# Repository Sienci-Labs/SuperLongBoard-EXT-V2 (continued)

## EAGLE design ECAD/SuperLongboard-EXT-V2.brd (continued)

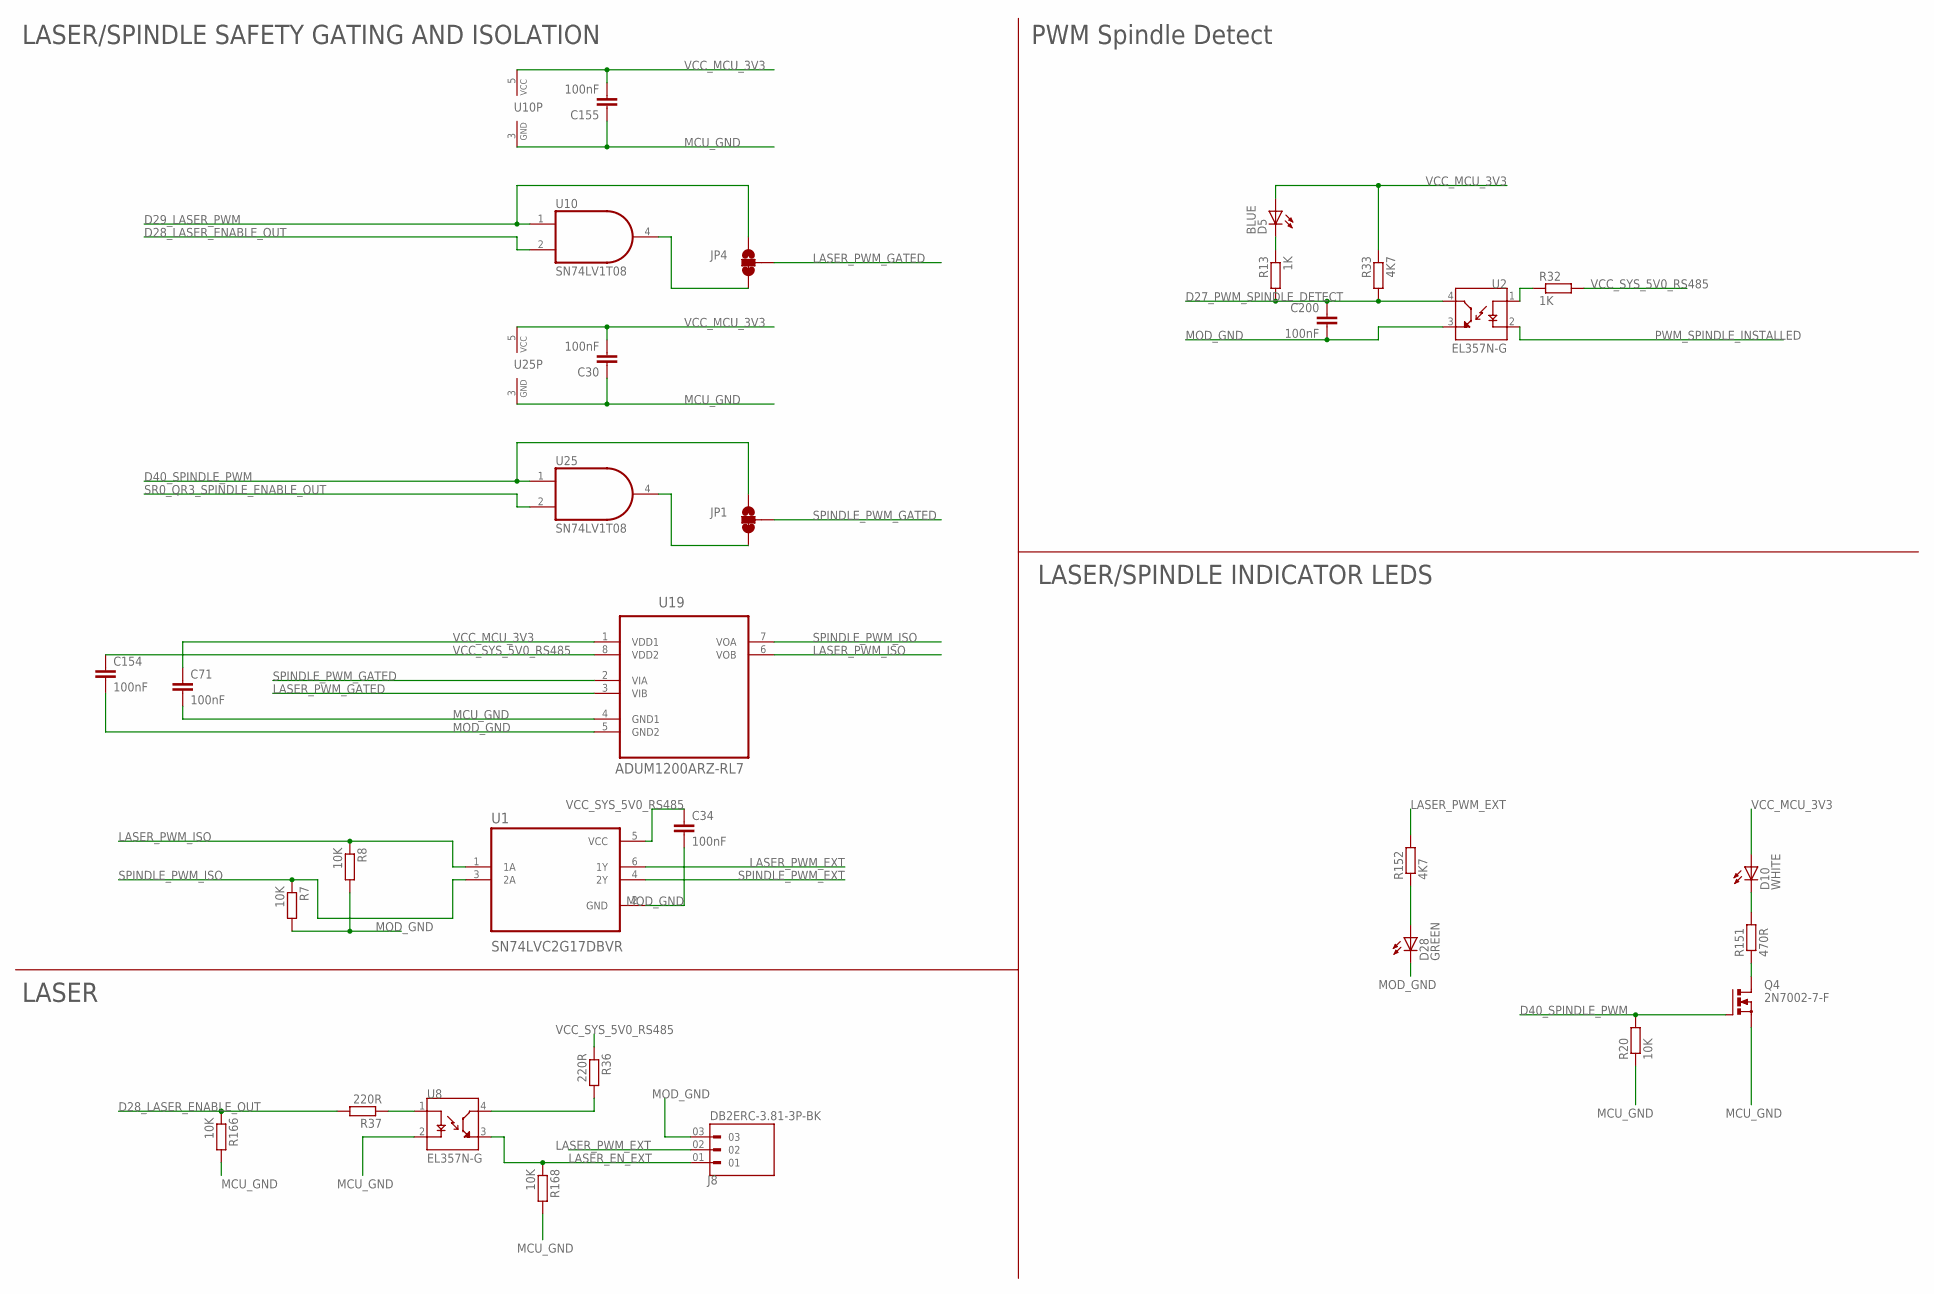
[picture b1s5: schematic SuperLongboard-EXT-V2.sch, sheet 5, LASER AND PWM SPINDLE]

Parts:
C30, C155, C200: 100nF; C0603
C34: 100nF; C0603; LCSC_PART C14663
C71, C154: 100nF; C0603K
D5: BLUE; CHIP-LED0805
D10: WHITE; CHIP-LED0805
D28: GREEN; CHIP-LED0805
J8: DB2ERC-3.81-3P-BK; PHOENIX_1803280
JP1, JP4: DNI; SMT-JUMPER_3_1-NC_TRACE_SILK
Q4: 2N7002-7-F; SOT-23
R7, R8, R20, R166, R168: 10K; R0603
R13, R32: 1K; R0603
R33, R152: 4K7; R0603
R36, R37: 220R; R0603
R151: 470R; R0603
U1: SN74LVC2G17DBVR; SOT95P280X145-6N
U2, U8: EL357N-G; OPTO_EL357N-G
U10, U25: SN74LV1T08; SOT23-5
U19: ADUM1200ARZ-RL7; SOIC127P600X175-8N

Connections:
D27_PWM_SPINDLE_DETECT: C200.1, R13.2, R33.2, U2.4 (CT); also elsewhere on the board
D28_LASER_ENABLE_OUT: R37.2, R166.1, U10.2 (I1); also elsewhere on the board
D29_LASER_PWM: JP4.1, U10.1 (I0); also elsewhere on the board
D40_SPINDLE_PWM: JP1.1, Q4.P1 (G), R20.2, U25.1 (I0); also elsewhere on the board
LASER_EN_EXT: J8.01, R168.1, U8.3 (ET)
LASER_PWM_EXT: J8.02, R152.2, U1.6 (1Y)
LASER_PWM_GATED: JP4.2, U19.3 (VIB)
LASER_PWM_ISO: R8.1, U1.1 (1A), U19.6 (VOB)
MCU_GND: C30.1, C71.2, C155.1, Q4.P2 (S), R20.1, R166.2, R168.2, U8.2 (C), U10.3 (GND), U19.4 (GND1), U25.3 (GND); also elsewhere on the board
MOD_GND: C34.2, C154.2, C200.2, D28.C, J8.03, R7.2, R8.2, U1.2 (GND), U2.3 (ET), U19.5 (GND2); also elsewhere on the board
unnamed: R32.1, U2.1 (A)
unnamed: JP1.3, U25.4 (O)
unnamed: D10.C, R151.2
unnamed: Q4.P3 (D), R151.1
unnamed: JP4.3, U10.4 (O)
unnamed: D5.C, R13.1
unnamed: D28.A, R152.1
unnamed: R37.1, U8.1 (A)
unnamed: R36.2, U8.4 (CT)
PWM_SPINDLE_INSTALLED: U2.2 (C); also elsewhere on the board
SPINDLE_PWM_EXT: U1.4 (2Y); also elsewhere on the board
SPINDLE_PWM_GATED: JP1.2, U19.2 (VIA)
SPINDLE_PWM_ISO: R7.1, U1.3 (2A), U19.7 (VOA)
SR0_QR3_SPINDLE_ENABLE_OUT: U25.2 (I1); also elsewhere on the board
VCC_MCU_3V3: C30.2, C71.1, C155.2, D5.A, D10.A, R33.1, U10.5 (VCC), U19.1 (VDD1), U25.5 (VCC); also elsewhere on the board
VCC_SYS_5V0_RS485: C34.1, C154.1, R32.2, R36.1, U1.5 (VCC), U19.8 (VDD2); also elsewhere on the board

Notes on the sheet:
LASER
PWM Spindle Detect
LASER/SPINDLE SAFETY GATING AND ISOLATION
LASER/SPINDLE INDICATOR LEDS

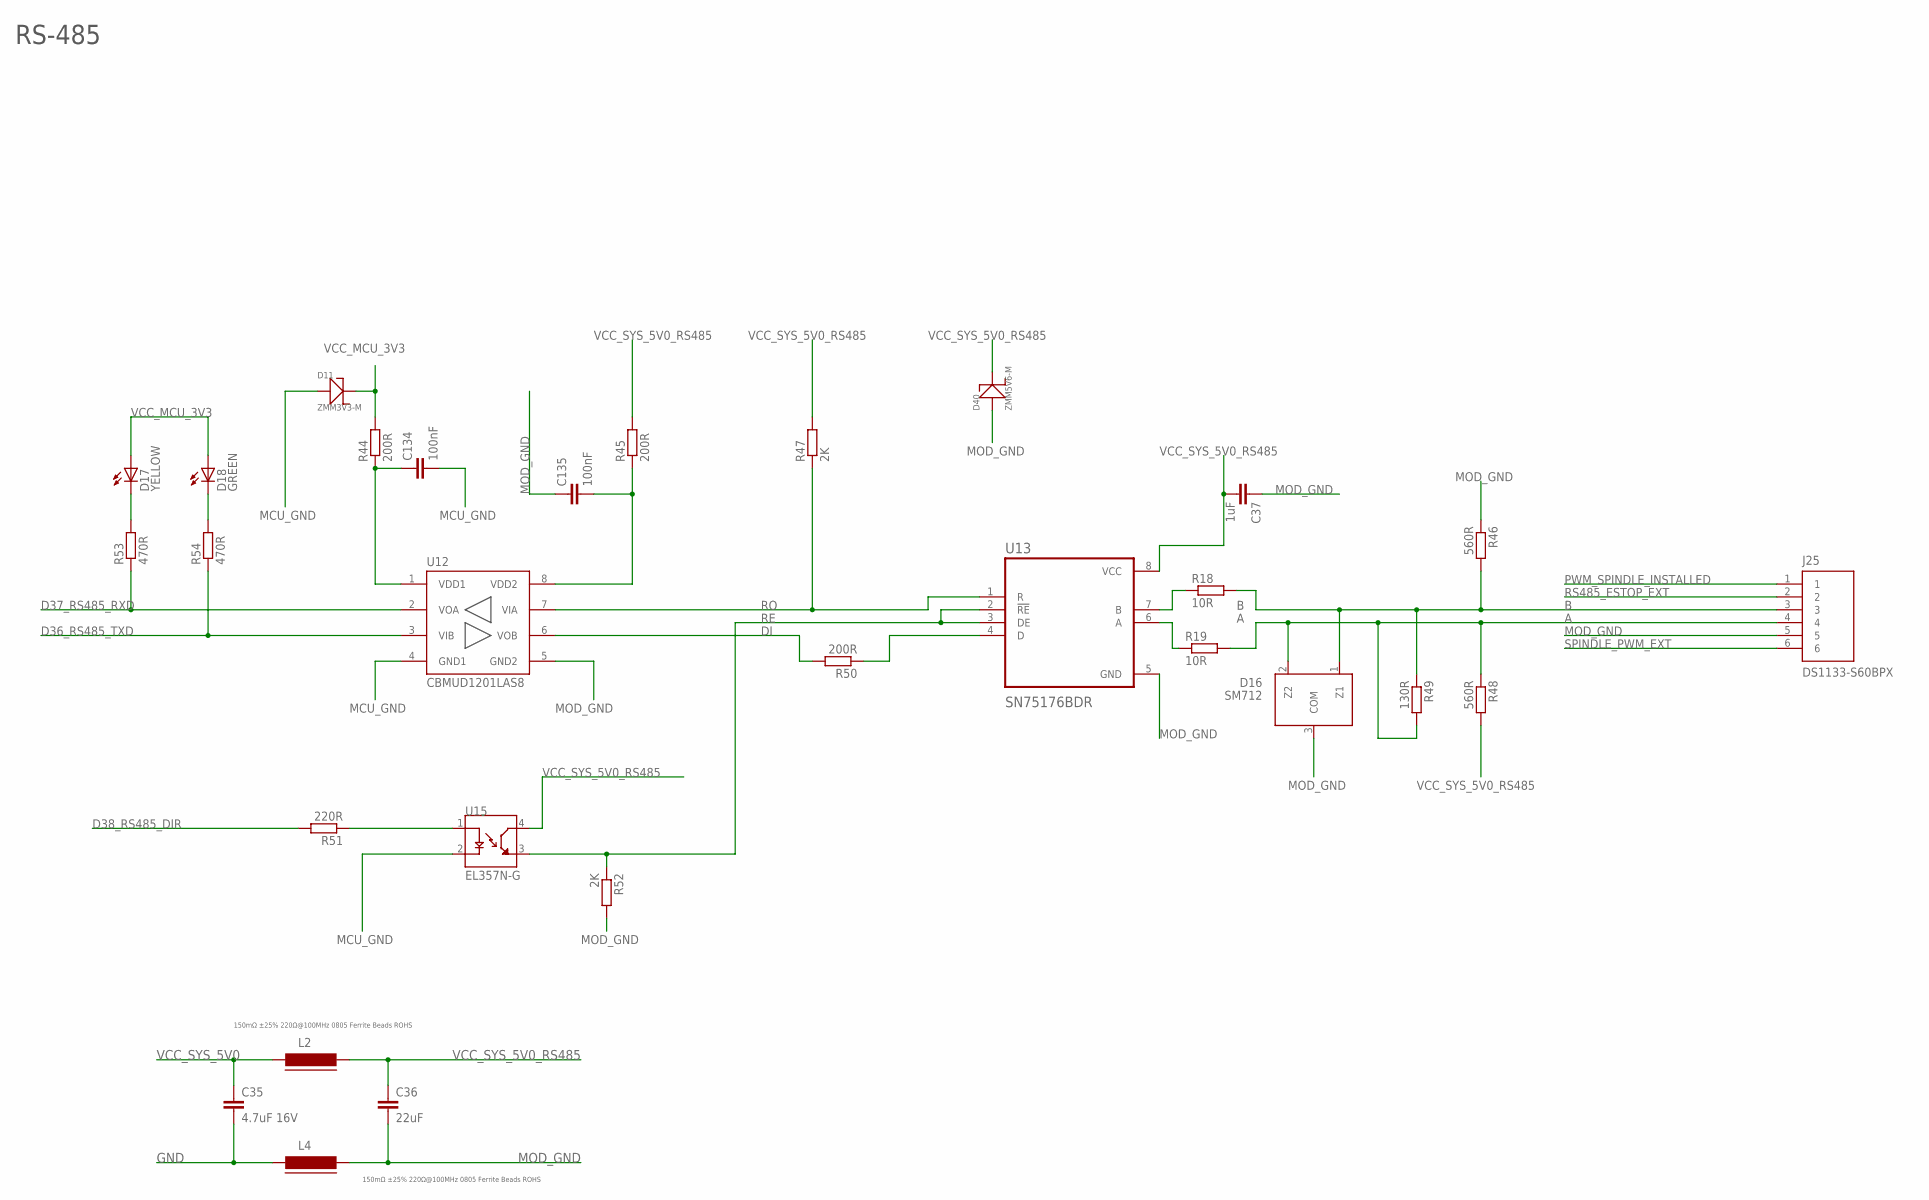
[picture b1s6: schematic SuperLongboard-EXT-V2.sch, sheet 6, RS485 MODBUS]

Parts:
C35: 4.7uF 16V; C0603
C36: 22uF; C0603; LCSC_PART C59461
C37: 1uF; C0603; LCSC_PART C15849
C134, C135: 100nF; C0603; LCSC_PART C14663
D11: ZMM3V3-M; LL-34
D16: SM712; SOT23
D17: YELLOW; CHIP-LED0805
D18: GREEN; CHIP-LED0805
D40: ZMM5V6-M; LL-34
J25: DS1133-S60BPX; KH-PCB-6P6C
L2, L4: 150mΩ ±25% 220Ω@100MHz 0805 Ferrite Beads ROHS; FB805; LCSC_PART C139188
R18, R19: 10R; R0603
R44, R45, R50: 200R; R0603
R46, R48: 560R; R0603
R47, R52: 2K; R0603
R49: 130R; R0805
R51: 220R; R0603
R53, R54: 470R; R0603
U12: CBMUD1201LAS8; SOIC-8
U13: SN75176BDR; SOIC127P599X175-8N
U15: EL357N-G; OPTO_EL357N-G

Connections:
A: D16.2 (Z2), J25.4, R19.2, R48.1, R49.2
B: D16.1 (Z1), J25.3, R18.2, R46.2, R49.1
D36_RS485_TXD: R54.1, U12.3 (VIB); also elsewhere on the board
D37_RS485_RXD: R53.1, U12.2 (VOA); also elsewhere on the board
D38_RS485_DIR: R51.2; also elsewhere on the board
DI: R50.2, U12.6 (VOB)
GND: C35.2, L4.1; also elsewhere on the board
MCU_GND: C134.2, D11.A (+), U12.4 (GND1), U15.2 (C); also elsewhere on the board
MOD_GND: C36.2, C37.1, C135.1, D16.3 (COM), D40.A (+), J25.5, L4.2, R46.1, R52.2, U12.5 (GND2), U13.5 (GND); also elsewhere on the board
unnamed: R18.1, U13.7 (B)
unnamed: R19.1, U13.6 (A)
unnamed: C134.1, R44.1, U12.1 (VDD1)
unnamed: C135.2, R45.1, U12.8 (VDD2)
unnamed: R50.1, U13.4 (D)
unnamed: R51.1, U15.1 (A)
unnamed: D17.C, R53.2
unnamed: D18.C, R54.2
PWM_SPINDLE_INSTALLED: J25.1; also elsewhere on the board
RE: R52.1, U13.2 (!RE), U13.3 (DE), U15.3 (ET)
RO: R47.1, U12.7 (VIA), U13.1 (R)
RS485_ESTOP_EXT: J25.2; also elsewhere on the board
SPINDLE_PWM_EXT: J25.6; also elsewhere on the board
VCC_MCU_3V3: D11.C (-), D17.A, D18.A, R44.2; also elsewhere on the board
VCC_SYS_5V0: C35.1, L2.1; also elsewhere on the board
VCC_SYS_5V0_RS485: C36.1, C37.2, D40.C (-), L2.2, R45.2, R47.2, R48.2, U13.8 (VCC), U15.4 (CT); also elsewhere on the board

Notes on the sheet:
RS-485

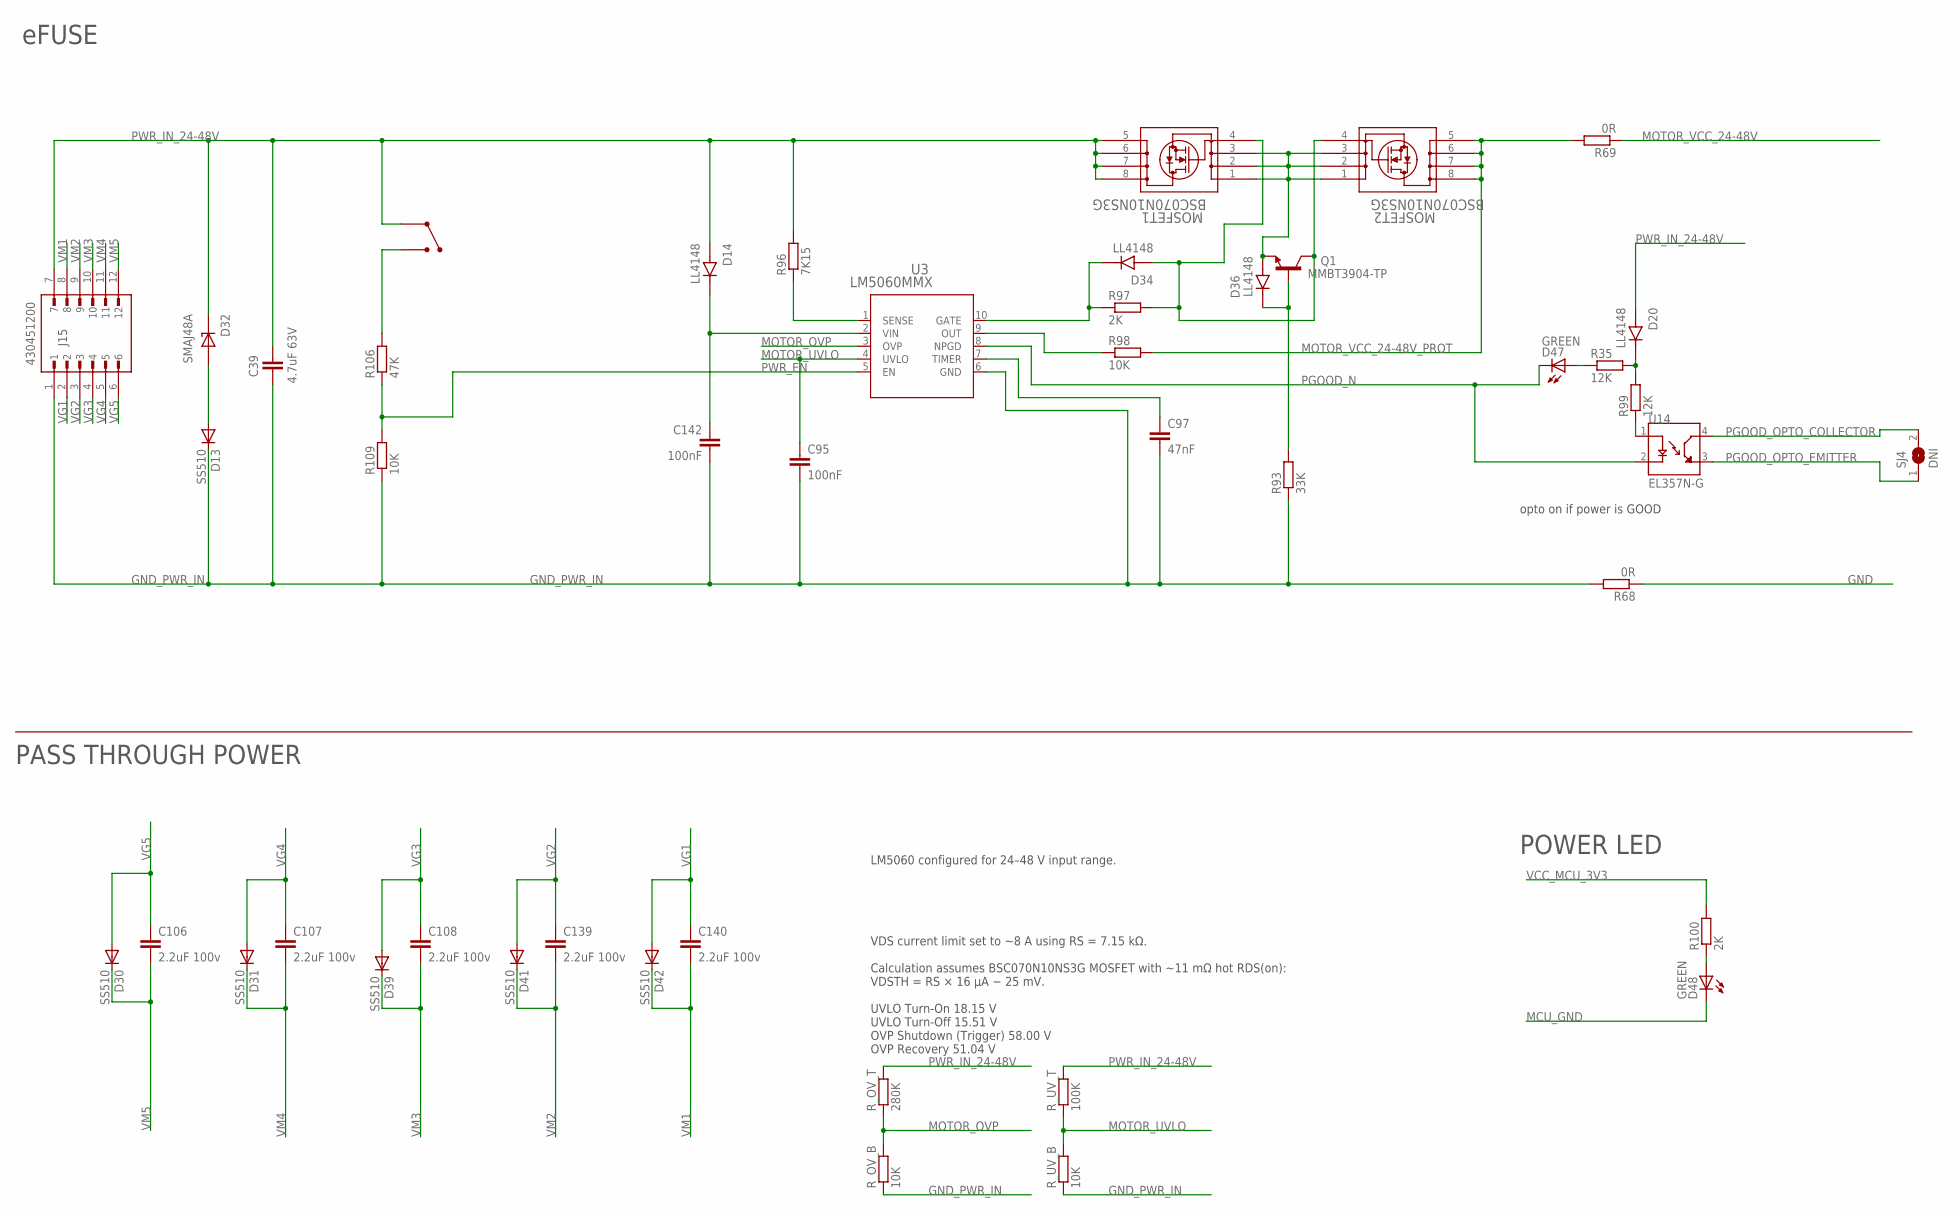
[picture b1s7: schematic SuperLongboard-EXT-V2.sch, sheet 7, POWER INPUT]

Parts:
C39: 4.7uF 63V; C1210; LCSC_PART C47783
C95, C142: 100nF; C0603; LCSC_PART C28233
C97: 47nF; C0805; LCSC_PART C53134
C106, C107, C108, C139, C140: 2.2uF 100v; C1210; LCSC_PART C576517
D13, D30, D31, D39, D41, D42: SS510; DO-214AC
D14, D20, D34, D36: LL4148; DIO_LL4148
D32: SMAJ48A; DIOM4325X250N
D47, D48: GREEN; CHIP-LED0805
J15: 430451200; MOLEX_430451200
MOSFET1, MOSFET2: BSC070N10NS3G; QNMOS_PRPAK5X6_HUA
Q1: MMBT3904-TP; SOT95P237X125-3N
R35, R99: 12K; R0805
R68, R69: 0R; R0603
R93: 33K; R0805
R96: 7K15; R1206
R97, R100: 2K; R0603
R98, R109: 10K; R0603
R106: 47K; R0805
R_OV_B: 10K; R0603
R_OV_T: 280K; R0805
R_UV_B: 10K; R0603
R_UV_T: 100K; R0805
SJ4: DNI; SJ
SW1: KCD11-BL
U3: LM5060MMX; MUB10A
U14: EL357N-G; OPTO_EL357N-G

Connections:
GND: R68.1; also elsewhere on the board
GND_PWR_IN: C39.2, C95.2, C97.2, C142.2, D13.C, J15.1, R68.2, R93.1, R109.1, R_OV_B.1, R_UV_B.1, U3.6 (GND)
MCU_GND: D48.C; also elsewhere on the board
MOTOR_OVP: R_OV_B.2, R_OV_T.1, U3.3 (OVP)
MOTOR_UVLO: C95.1, R_UV_B.2, R_UV_T.1, U3.4 (UVLO)
MOTOR_VCC_24-48V: R69.1; also elsewhere on the board
MOTOR_VCC_24-48V_PROT: MOSFET2.5, MOSFET2.6, MOSFET2.7, MOSFET2.8, R69.2, R98.2
unnamed: D47.A, R35.1
unnamed: R96.1, U3.1 (SENSE)
unnamed: D34.C, R97.1, U3.10 (GATE)
unnamed: D36.C, Q1.1 (B), R93.2
unnamed: R98.1, U3.9 (OUT)
unnamed: C97.1, U3.7 (TIMER)
unnamed: D20.C, R35.2, R99.2
unnamed: D34.A, MOSFET1.4, MOSFET2.4, Q1.3 (C), R97.2
unnamed: C142.1, D14.C, U3.2 (VIN)
unnamed: D13.A, D32.A
unnamed: R99.1, U14.1 (A)
unnamed: D36.A, MOSFET1.1, MOSFET1.2, MOSFET1.3, MOSFET2.1, MOSFET2.2, MOSFET2.3, Q1.2 (E)
unnamed: D48.A, R100.1
unnamed: R106.2, SW1.P$2
PGOOD_N: D47.C, U3.8 (NPGD), U14.2 (C)
PGOOD_OPTO_COLLECTOR: SJ4.2, U14.4 (CT); also elsewhere on the board
PGOOD_OPTO_EMITTER: SJ4.1, U14.3 (ET); also elsewhere on the board
PWR_EN: R106.1, R109.2, U3.5 (EN)
PWR_IN_24-48V: C39.1, D14.A, D20.A, D32.C, J15.7, MOSFET1.5, MOSFET1.6, MOSFET1.7, MOSFET1.8, R96.2, R_OV_T.2, R_UV_T.2, SW1.P$1
VCC_MCU_3V3: R100.2; also elsewhere on the board
VG1: C140.1, D42.A, J15.2; also elsewhere on the board
VG2: C139.1, D41.A, J15.3; also elsewhere on the board
VG3: C108.1, D39.A, J15.4; also elsewhere on the board
VG4: C107.1, D31.A, J15.5; also elsewhere on the board
VG5: C106.1, D30.A, J15.6; also elsewhere on the board
VM1: C140.2, D42.C, J15.8; also elsewhere on the board
VM2: C139.2, D41.C, J15.9; also elsewhere on the board
VM3: C108.2, D39.C, J15.10; also elsewhere on the board
VM4: C107.2, D31.C, J15.11; also elsewhere on the board
VM5: C106.2, D30.C, J15.12; also elsewhere on the board

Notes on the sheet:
eFUSE
LM5060 configured for 24–48 V input range. VDS current limit set to ~8 A using RS = 7.15 kΩ. Calculation assumes BSC070N10NS3G MOSFET with ~11 mΩ hot RDS(on): VDSTH = RS × 16 µA − 25 mV. UVLO Turn-On 18.15 V UVLO Turn-Off 15.51 V OVP Shutdown (Trigger) 58.00 V OVP Recovery 51.04 V
opto on if power is GOOD
POWER LED
PASS THROUGH POWER

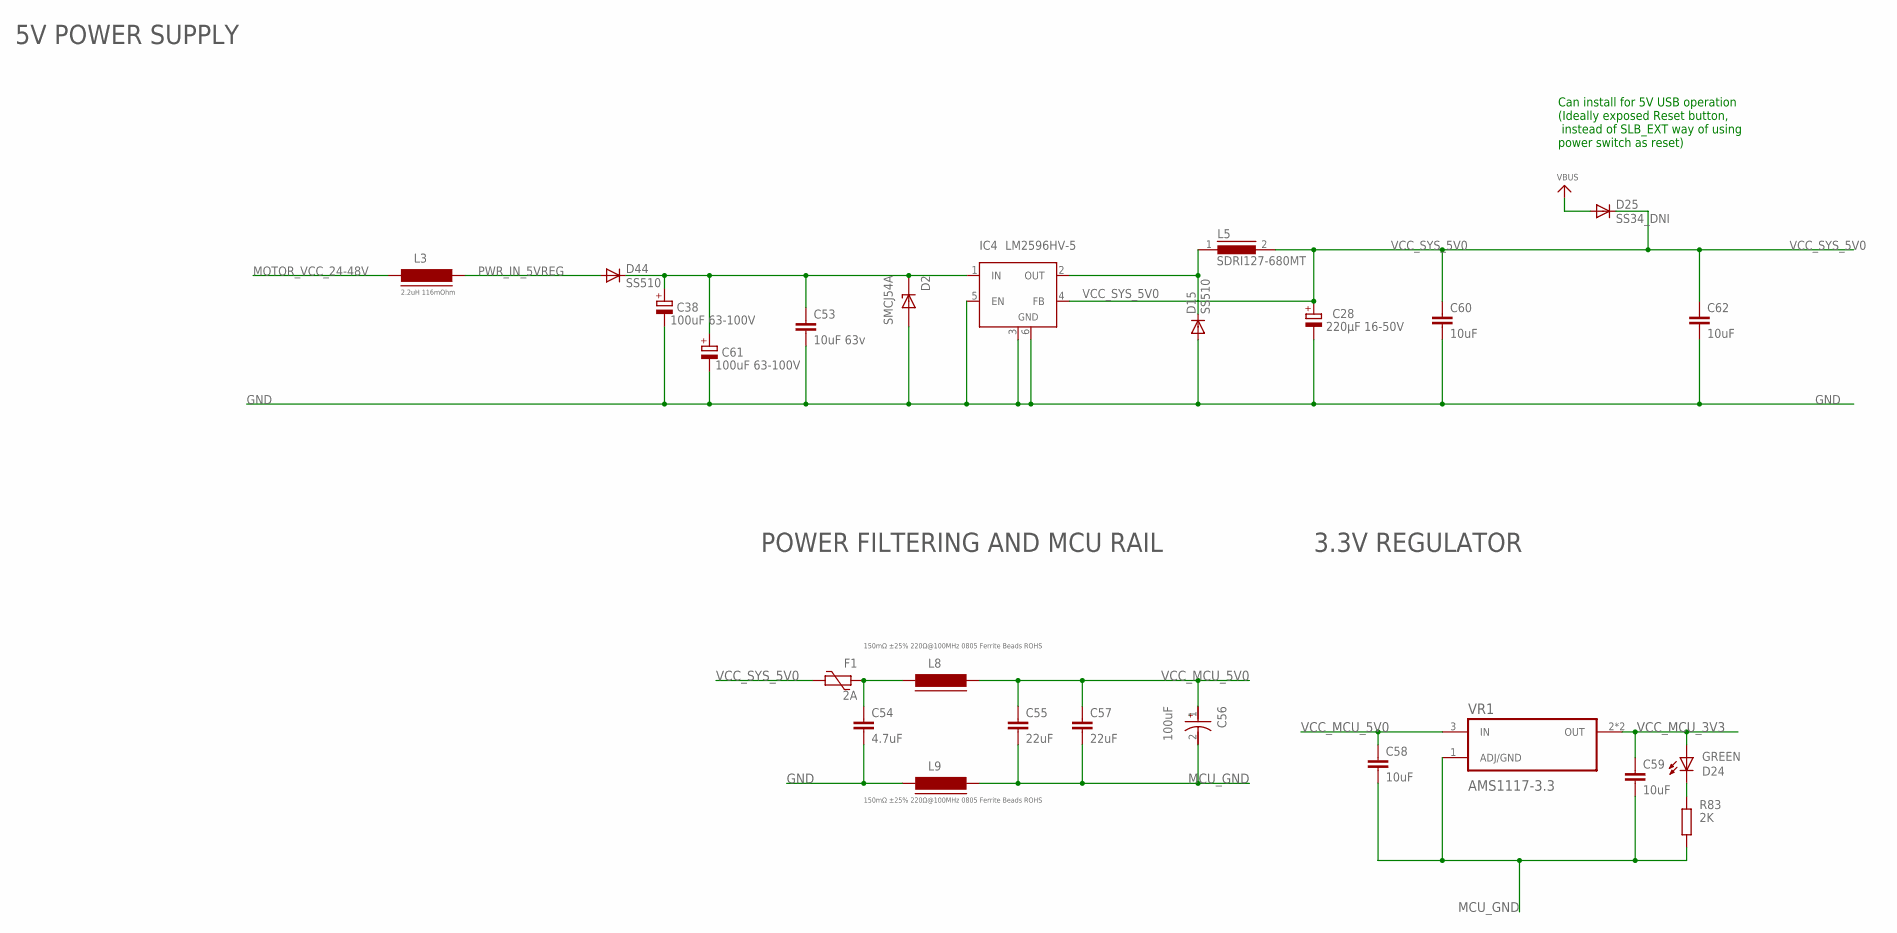
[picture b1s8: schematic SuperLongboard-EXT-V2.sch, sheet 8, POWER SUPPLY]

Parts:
C28: 220µF 16-50V; PANASONIC_E
C38, C61: 100uF 63-100V; PANASONIC_E
C53: 10uF 63v; C1206; LCSC_PART C13585
C54: 4.7uF; C0603
C55, C57: 22uF; C0603; LCSC_PART C59461
C56: 100uF; CAPMP3528X210N
C58, C59, C60, C62: 10uF; C1206; LCSC_PART C13585
D2: SMCJ54A; DIOM7959X262N
D15, D44: SS510; DO-214AC
D24: GREEN; CHIP-LED0805
D25: SS34_DNI; DO-214AC
F1: 2A; 1206L
IC4: LM2596HV-5; TO263-5
L3: 2.2uH 116mOhm; FB805; LCSC_PART C139188
L5: SDRI127-680MT; DR127
L8, L9: 150mΩ ±25% 220Ω@100MHz 0805 Ferrite Beads ROHS; FB805; LCSC_PART C139188
R83: 2K; R0603
VR1: AMS1117-3.3

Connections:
+24V1: C38.+, C53.1, C61.+, D2.C, D44.C, IC4.1 (IN)
GND: C28.-, C38.-, C53.2, C54.2, C60.2, C61.-, C62.2, D2.A, D15.A, IC4.3 (GND), IC4.5 (EN), IC4.6 (GND), L9.1; also elsewhere on the board
MCU_GND: C55.2, C56.2, C57.2, C58.2, C59.2, L9.2, R83.2, VR1.1 (ADJ/GND); also elsewhere on the board
MOTOR_VCC_24-48V: L3.1; also elsewhere on the board
unnamed: D24.C, R83.1
unnamed: D15.C, IC4.2 (OUT), L5.1
PWR_IN_5VREG: D44.A, L3.2
SYS5V: C54.1, F1.2, L8.1
VBUS: D25.A; also elsewhere on the board
VCC_MCU_3V3: C59.1, D24.A, VR1.2 (OUT), VR1.4 (OUT); also elsewhere on the board
VCC_MCU_5V0: C55.1, C56.1, C57.1, C58.1, L8.2, VR1.3 (IN)
VCC_SYS_5V0: C28.+, C60.1, C62.1, D25.C, F1.1, IC4.4 (FB), L5.2; also elsewhere on the board

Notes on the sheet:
POWER FILTERING AND MCU RAIL
3.3V REGULATOR
5V POWER SUPPLY
Can install for 5V USB operation (Ideally exposed Reset button, instead of SLB_EXT way of using power switch as reset)

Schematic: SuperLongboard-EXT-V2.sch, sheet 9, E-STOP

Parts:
C3, C9, C13, C19, C20, C29, C31: 100nF; C0603; LCSC_PART C14663
D2_ESTOP_MCU: RED; CHIP-LED0805
E_STOPIN: 74HC08D-T; SOIC127P600X175-14N
J10: B2B-XH-A_(LF)(SN); JST_B2B-XH-A_(LF)(SN)
J11: DB2ERC-3.81-2P-BK; MC1.5/2-G-3.81
JP2: DNI; SMT-JUMPER_3_1-NC_TRACE_SILK
L12: 150mΩ ±25% 220Ω@100MHz 0805 Ferrite Beads ROHS; FB805; LCSC_PART C139188
R2, R34, R43, R56, R58, R64: 10K; R0603
R30, R40, R57: 510R; R0603
R38, R41: 120R; R0603
R55: 220R; R0603
R61: 2K; R0603
U11, U16, U22, U23: EL357N-G; OPTO_EL357N-G
U20_EGATE: 74HC08D-T; SOIC127P600X175-14N

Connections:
D28_LASER_ENABLE: U20_EGATE.2 (1B); also elsewhere on the board
D28_LASER_ENABLE_OUT: U20_EGATE.3 (1Y); also elsewhere on the board
D39_E_STOP/HALT: C19.1, E_STOPIN.11 (4Y), R61.1, R64.1, U20_EGATE.1 (1A), U20_EGATE.4 (2A), U20_EGATE.9 (3A), U20_EGATE.12 (4A), U22.2 (C); also elsewhere on the board
ESTOP1_LV: C13.1, E_STOPIN.1 (1A), R56.2, U16.3 (ET)
ESTOP3_LV: C3.1, E_STOPIN.4 (2A), R34.1, U11.4 (CT)
ESTOP5_LV: C31.1, E_STOPIN.9 (3A), R58.1, U23.4 (CT)
ESTOP_AUX: U11.2 (C); also elsewhere on the board
ESTOP_CONTROLLER: J10.1, R40.2
ESTOP_EXT: J11.1, R57.2
GND: U16.2 (C), U23.2 (C); also elsewhere on the board
MCU_GND: C3.2, C9.2, C13.2, C19.2, C20.2, C29.2, C31.2, E_STOPIN.7 (GND), R2.1, R56.1, U11.3 (ET), U20_EGATE.7 (GND), U23.3 (ET); also elsewhere on the board
MOD_GND: U22.3 (ET); also elsewhere on the board
unnamed: R30.1, U11.1 (A)
unnamed: R55.1, U22.1 (A)
unnamed: R40.1, U16.1 (A)
unnamed: E_STOPIN.6 (2Y), E_STOPIN.10 (3B)
unnamed: E_STOPIN.3 (1Y), E_STOPIN.12 (4A)
unnamed: E_STOPIN.8 (3Y), E_STOPIN.13 (4B)
unnamed: R41.1, U16.4 (CT)
unnamed: R57.1, U23.1 (A)
unnamed: D2_ESTOP_MCU.C, R61.2
unnamed: JP2.1, U20_EGATE.11 (4Y)
PGOOD_OPTO_COLLECTOR: R38.1; also elsewhere on the board
PGOOD_OPTO_EMITTER: C9.1, E_STOPIN.2 (1B), R2.2; also elsewhere on the board
RS485_ESTOP_EXT: U22.4 (CT); also elsewhere on the board
SPARE_ESTOP: E_STOPIN.5 (2B), R43.1
SR0_Q0_XYA_ENABLE: U20_EGATE.10 (3B); also elsewhere on the board
SR0_Q0_XYA_ENABLE_OUT: U20_EGATE.8 (3Y); also elsewhere on the board
SR0_Q1_Z_ENABLE: JP2.3, U20_EGATE.13 (4B); also elsewhere on the board
SR0_Q1_Z_ENABLE_OUT: JP2.2; also elsewhere on the board
SR0_QR3_SPINDLE_ENABLE: U20_EGATE.5 (2B); also elsewhere on the board
SR0_QR3_SPINDLE_ENABLE_OUT: U20_EGATE.6 (2Y); also elsewhere on the board
VCC_ESTOP_5V0: J10.2, J11.2, L12.1, R30.2
VCC_MCU_3V3: C20.1, C29.1, D2_ESTOP_MCU.A, E_STOPIN.14 (VCC), R34.2, R38.2, R41.2, R43.2, R55.2, R58.2, R64.2, U20_EGATE.14 (VCC); also elsewhere on the board
VCC_SYS_5V0: L12.2; also elsewhere on the board

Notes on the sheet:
HIGH - IF NO ESTOPS ARE ACTIVATED LOW - IF ANY ESTOP IS ACTIVATED
EMERGENCY STOPS
SIGNAL TO GRBLHAL
GATED ENABLE SIGNALS FOR CLS MOTORS, LASER, PWM SPINDLE
E-STOP OUTPUT FOR RS485 SPINDLE
PRIMARY E-STOP INPUT - CLOSED LOOP - OPENS ON PROBLEM
SIGNALS FROM MCU TO BE GATED BY E-STOP
PGOOD E-STOP INPUT -CLOSED LOOP - OPENS ON PROBLEM
AUX/ATCPTC E-STOP INPUT - OPEN LOOP - CLOSES ON PROBLEM
EXTERNAL/PANEL MOUNT/REMOTE E-STOP INPUT OPEN LOOP - CLOSES ON PROBLEM

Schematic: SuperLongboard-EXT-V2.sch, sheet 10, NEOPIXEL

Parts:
C101, C102: 100nF; C0603; LCSC_PART C14663
F4: 2A; 1206L
J6, J16: B3B-XH-A(LF)(SN); JST_B3B-XH-A(LF)(SN)
WC4, WC5, WC6, WC7, WC8, WC9, WC10, WC11, WC12, WC13, WC14, WC15: 100nF; C0603; LCSC_PART C14663
WL4, WL5, WL6, WL7, WL8, WL9, WL10, WL11, WL12, WL13, WL14, WL15: WS2812-2020; LED_WS2812-2020

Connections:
D35_NEOPIXEL_OUT: WL4.3 (DIN); also elsewhere on the board
GND: C101.2, C102.2, J6.1, J16.1, WC4.2, WC5.2, WC6.2, WC7.2, WC8.2, WC9.2, WC10.2, WC11.2, WC12.2, WC13.2, WC14.2, WC15.2, WL4.2 (VSS), WL5.2 (VSS), WL6.2 (VSS), WL7.2 (VSS), WL8.2 (VSS), WL9.2 (VSS), WL10.2 (VSS), WL11.2 (VSS), WL12.2 (VSS), WL13.2 (VSS), WL14.2 (VSS), WL15.2 (VSS); also elsewhere on the board
unnamed: WL4.1 (DOUT), WL5.3 (DIN)
unnamed: WL5.1 (DOUT), WL6.3 (DIN)
unnamed: WL6.1 (DOUT), WL7.3 (DIN)
unnamed: WL7.1 (DOUT), WL8.3 (DIN)
unnamed: WL8.1 (DOUT), WL9.3 (DIN)
unnamed: WL9.1 (DOUT), WL10.3 (DIN)
unnamed: WL10.1 (DOUT), WL11.3 (DIN)
unnamed: WL11.1 (DOUT), WL12.3 (DIN)
unnamed: WL12.1 (DOUT), WL13.3 (DIN)
unnamed: WL13.1 (DOUT), WL14.3 (DIN)
unnamed: WL14.1 (DOUT), WL15.3 (DIN)
unnamed: J6.2, J16.2, WL15.1 (DOUT)
NEOPIXEL_5V: C101.1, C102.1, F4.2, J6.3, J16.3, WC4.1, WC5.1, WC6.1, WC7.1, WC8.1, WC9.1, WC10.1, WC11.1, WC12.1, WC13.1, WC14.1, WC15.1, WL4.4 (VDD), WL5.4 (VDD), WL6.4 (VDD), WL7.4 (VDD), WL8.4 (VDD), WL9.4 (VDD), WL10.4 (VDD), WL11.4 (VDD), WL12.4 (VDD), WL13.4 (VDD), WL14.4 (VDD), WL15.4 (VDD)
VCC_SYS_5V0: F4.1; also elsewhere on the board

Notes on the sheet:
NEOPIXELS

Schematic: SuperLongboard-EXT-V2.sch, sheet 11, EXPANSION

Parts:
C93: 100nF; C0603; LCSC_PART C14663
IC1_SREXP: 74HC595; SOIC-16
J5: Connector IDC Header Through Hole 26 position 2.5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; 61202621621
R6, R59, R82: 100R; R0603
R65: 10k; R0603
R70: 100K; R0805

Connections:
D0_UART0_RX: J5.5; also elsewhere on the board
D1_UART0_TX: J5.7; also elsewhere on the board
D26_SR0_OE: IC1_SREXP.13 (!OE), J5.21, R65.1; also elsewhere on the board
D30_SDA: J5.11; also elsewhere on the board
D31_SCL: J5.13; also elsewhere on the board
D32_SR0_OUT: R6.1; also elsewhere on the board
D33_SR0_SCK: J5.15, R82.1; also elsewhere on the board
D34_SR0_LCK: J5.17, R59.1; also elsewhere on the board
D35_NEOPIXEL: J5.9; also elsewhere on the board
D41_ETHERNET_CS: J5.8, R70.1; also elsewhere on the board
D42_ETHERNET_IRQ: J5.10; also elsewhere on the board
D43_SPI_MOSI: J5.4; also elsewhere on the board
D44_SPI_MISO: J5.2; also elsewhere on the board
D46_SPI_SCK: J5.6; also elsewhere on the board
D47_SPARE: J5.14; also elsewhere on the board
ESTOP_AUX: J5.23; also elsewhere on the board
GND: C93.2, J5.1, J5.12, J5.26, R70.2; also elsewhere on the board
MCU_GND: IC1_SREXP.8 (GND); also elsewhere on the board
MOTOR_VCC_24-48V: J5.25; also elsewhere on the board
unnamed: IC1_SREXP.12 (LATCH), R59.2
unnamed: IC1_SREXP.11 (SCLK), R82.2
unnamed: IC1_SREXP.14 (SDA), R6.2
SR0_OUT: IC1_SREXP.9 (Q7S), J5.19
SR0_Q0_XYA_ENABLE: IC1_SREXP.15 (Q0); also elsewhere on the board
SR0_Q1_Z_ENABLE: IC1_SREXP.1 (Q1); also elsewhere on the board
SR0_Q2_COOLANT: IC1_SREXP.2 (Q2); also elsewhere on the board
SR0_QR3_SPINDLE_ENABLE: IC1_SREXP.3 (Q3), J5.16; also elsewhere on the board
SR0_QR4_SPARE: IC1_SREXP.4 (Q4), J5.18
SR0_QR5_SPARE: IC1_SREXP.5 (Q5), J5.20
SR0_QR6_SPARE: IC1_SREXP.6 (Q6), J5.22
SR0_QR7_SPARE: IC1_SREXP.7 (Q7), J5.24
VCC_MCU_3V3: C93.1, IC1_SREXP.10 (!RST), IC1_SREXP.16 (V+), R65.2; also elsewhere on the board
VCC_SYS_5V0: J5.3; also elsewhere on the board

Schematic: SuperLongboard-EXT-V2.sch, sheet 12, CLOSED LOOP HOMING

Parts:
C32, C52: 100nF; C0603K
D19, D29: GREEN; CHIP-LED0805
R39, R42: 200R; R0603
R60, R74: 2K; R0603
R62, R75: 10K; R0603
U4: ADUM1200ARZ-RL7; SOIC127P600X175-8N

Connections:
D24_XYA_HOME_EN: D19.C, R75.1, U4.2 (VIA); also elsewhere on the board
D25_Z_HOME_EN: D29.C, R62.1, U4.3 (VIB); also elsewhere on the board
GND: C52.2, U4.5 (GND2); also elsewhere on the board
MCU_GND: C32.2, U4.4 (GND1); also elsewhere on the board
unnamed: R39.2, U4.7 (VOA)
unnamed: R42.2, U4.6 (VOB)
unnamed: D29.A, R60.1
unnamed: D19.A, R74.1
VCC_MCU_3V3: C32.1, R60.2, R62.2, R74.2, R75.2, U4.1 (VDD1); also elsewhere on the board
VCC_SYS_5V0: C52.1, U4.8 (VDD2); also elsewhere on the board
XYA_HOME_EN: R39.1; also elsewhere on the board
Z_HOME_EN: R42.1; also elsewhere on the board

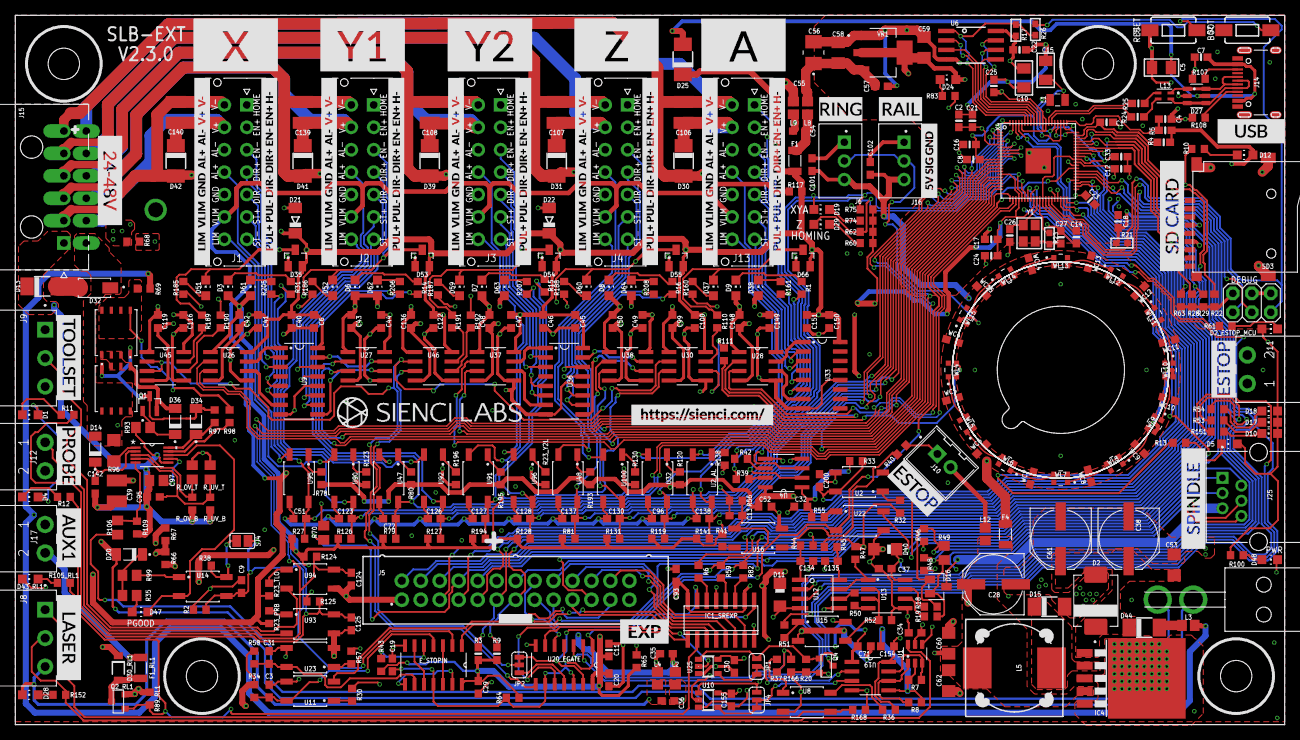
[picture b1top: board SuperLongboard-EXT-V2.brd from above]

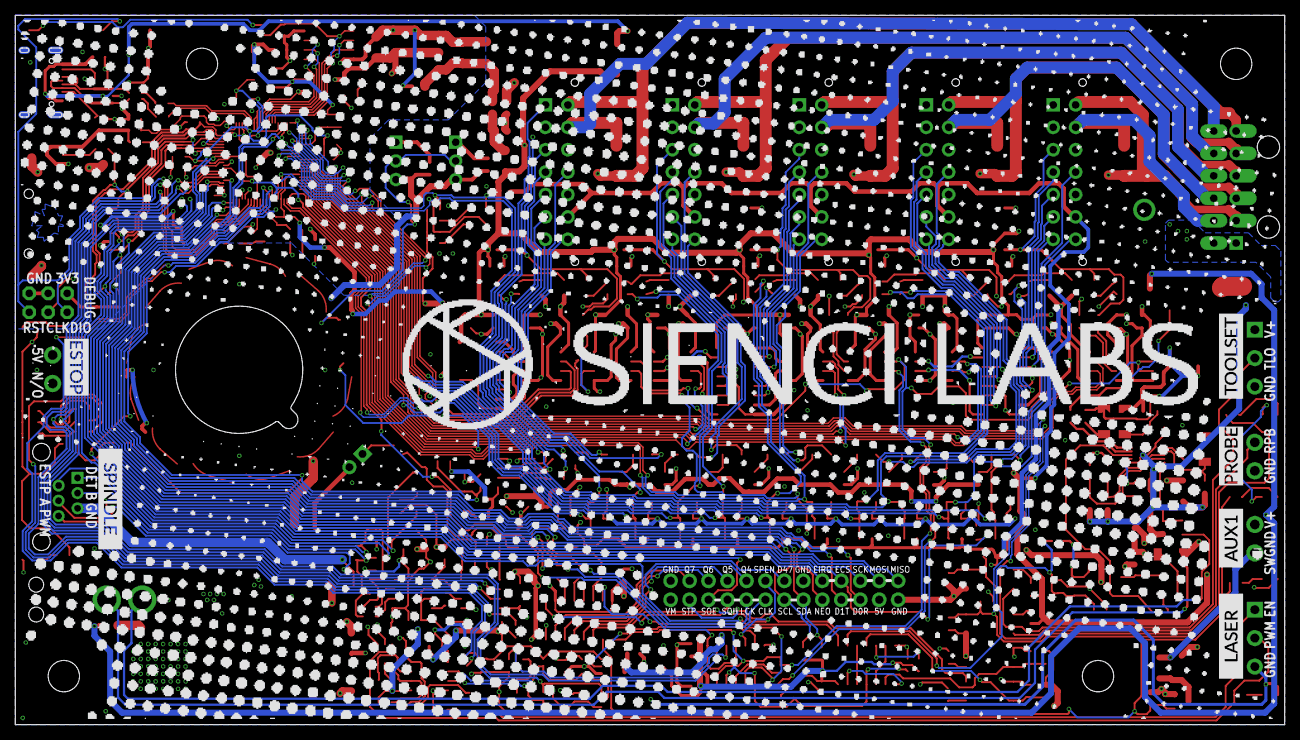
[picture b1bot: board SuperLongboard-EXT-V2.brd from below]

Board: 4 copper layers, 170.0 x 95.0 mm, 441 parts (6 on the bottom side), 293 nets.

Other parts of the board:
U$1: Z
U$3, U$6, U$18, U$21, U$26: LIM__VLIM__GND__AL#__AL#__V#__V#
U$4, U$36: AUX1
U$5, U$17, U$20, U$22, U$27: PUL#_PUL#_DIR#_DIR#_EN#_EN#_H#
U$7, U$13, U$39: ESTOP
U$8, U$37: LASER
U$9, U$34: TOOLSET
U$10, U$35: PROBE
U$11, U$38: SPINDLE
U$12: RAIL
U$14: RING
U$16: SD_CARD
U$19: USB
U$23: Y1
U$24: Y2
U$25: X
U$28: 5V_SIG_GND
U$30: EXP
U$31: A
U$32: HTTPS###SIENCI#COM#
U$33: 24#48V
